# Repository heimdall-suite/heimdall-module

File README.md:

# heimdall-module

ESP32-C3 based module for the transmitter's JR module bay, part of the Heimdall Suite.

## Status

Hardware rev 2 (KiCad 10, `hardware/kicad/`): schematic reviewed and corrected,
board re-placed and re-routed from the first EasyEDA layout. Not built or tested
yet. The EasyEDA originals are kept in `hardware/easyeda-archive/`. No firmware yet.

KiCad 3D renders of rev 2:

| Top, angled | Bottom, angled |
|---|---|
|  |  |

| Top | Bottom (mirrored, as seen from below) |
|---|---|
|  |  |

## Case

The board is shaped for the 3D-printed case `MULTI-Module_Bangood_4-in-1_Case.stl`
(the STL is not in this repo). The figures below were measured from that STL:

- The outline is the case cavity (57 x 41.5 mm) minus 0.3 mm all round. It has
  notches for the two latch housings, which reach 4 mm in from the long walls.
  The top notch merges with the cut-out under the ESP32 module's antenna.
- The four corners are chamfered 45° (2.8 mm legs). The lid screw holes
  (1.7 mm) sit in 3.5 mm bosses in the cavity corners, from about 11 mm above
  the floor upwards. The board has to pass them on the way down to the
  standoffs, and the chamfers leave about 0.47 mm to each boss.
- MH1-MH3 are 2.2 mm holes for 2 mm self-tapping screws into the case's three
  standoffs (4.5 mm, 1.8 mm pilot holes, tops 5 mm above the floor).
  The lid uses the same screws. The copper keeps 3 mm clear of each hole.
- The bay pins come up through the floor opening and the H1 slot into the
  female header on top.
- **H1 position:** taken from three existing JR-bay designs. All three put the
  bay pins about 1.25 mm closer to the end wall than the centre of the case's
  floor opening:
  - DIY Multiprotocol STM32 v1.0t (Eagle)
  - Multiprotocol V2 (Gerbers)
  - ExpressLRS TX_SX1280 (Gerbers)

  This is not yet checked against a real radio.
- The case still needs an opening for the USB-C connector.

`case_place.py` moved the rev 2 parts into the case outline. `spread_place.py`
then spread them for hand soldering: at least 1 mm between courtyards left of the
module, and U1 moved down to the bottom edge. A few pairs on the USB side are
still closer. `route_pcb.py prep` draws the hand routes; Freerouting and the
later `route_pcb.py` steps do the rest.

## Pin assignment (rev 2)

| Function | ESP32-C3 GPIO | Via |
|---|---|---|
| Bay SIGNAL / PPM (H1 pin 1), input | IO4 | D3, R11 4.7k pull-up |
| Bay DATA / S.Port (H1 pin 5), receive | IO5 | D4, R13 4.7k pull-up |
| Bay DATA / S.Port (H1 pin 5), transmit | IO7 | U5 74LVC1G34 + R14 1k |
| Bay HB (H1 pin 2), output | IO8 | D5 (pull low only), R9 doubles as its pull-up |
| I2C SDA / SCL (J1, 10k pull-ups) | GPIO20 / GPIO21 (U0RXD / U0TXD) | |
| Breakout (J1) | IO1, IO3, IO10 | |
| USB D- / D+ | IO18 / IO19 | R4 / R3 33R |
| Strapping | IO2, IO8 (HB), IO9 pulled up 10k; JP1 BOOT bridges IO9 to GND | |

IO0 and IO6 are unused. UART0's pins carry I2C, so the console has to run over
USB-Serial/JTAG.

## Bay interface

The bay lines never connect straight to the ESP32.

- SIGNAL (PPM in) and DATA receive go through a BAT54WS Schottky with its
  cathode at the bay, the same scheme as the DIY Multiprotocol module (STM32
  board v1.0t, BAT48 diodes). The radio can only pull the line low; the high
  level comes from our 3V3 pull-ups (R11, R13), so a radio that drives 5 V
  never reaches the ESP32.
- HB (out) goes through a Schottky with its anode at the bay: the ESP32 can
  only pull it low, R12 (4.7k) pulls it high on the bay side.
- DATA transmit goes through U5, a 74LVC1G34 buffer (5.5 V tolerant, always on),
  and R14 (1k). The UART's idle level holds the line, so the same hardware
  works for CRSF (idle high) and inverted S.Port (idle low); which one is a
  firmware setting. When the radio transmits it overrides the 1k (about
  3.3 mA). Against a 10k pull-up on the radio side, an S.Port idle low sits at
  about 0.3 V (calculated, not measured).

DATA is half duplex on one wire, with separate receive and transmit pins
(IO5/IO7). The receive pin also sees the module's own transmitted bytes, so
firmware has to discard that echo. Inversion is done in the ESP32-C3's UART.
Use IO8 (HB) as an output only after boot: it is a strapping pin, which is
safe here because download mode needs USB, and USB and the bay can't be
connected at the same time.

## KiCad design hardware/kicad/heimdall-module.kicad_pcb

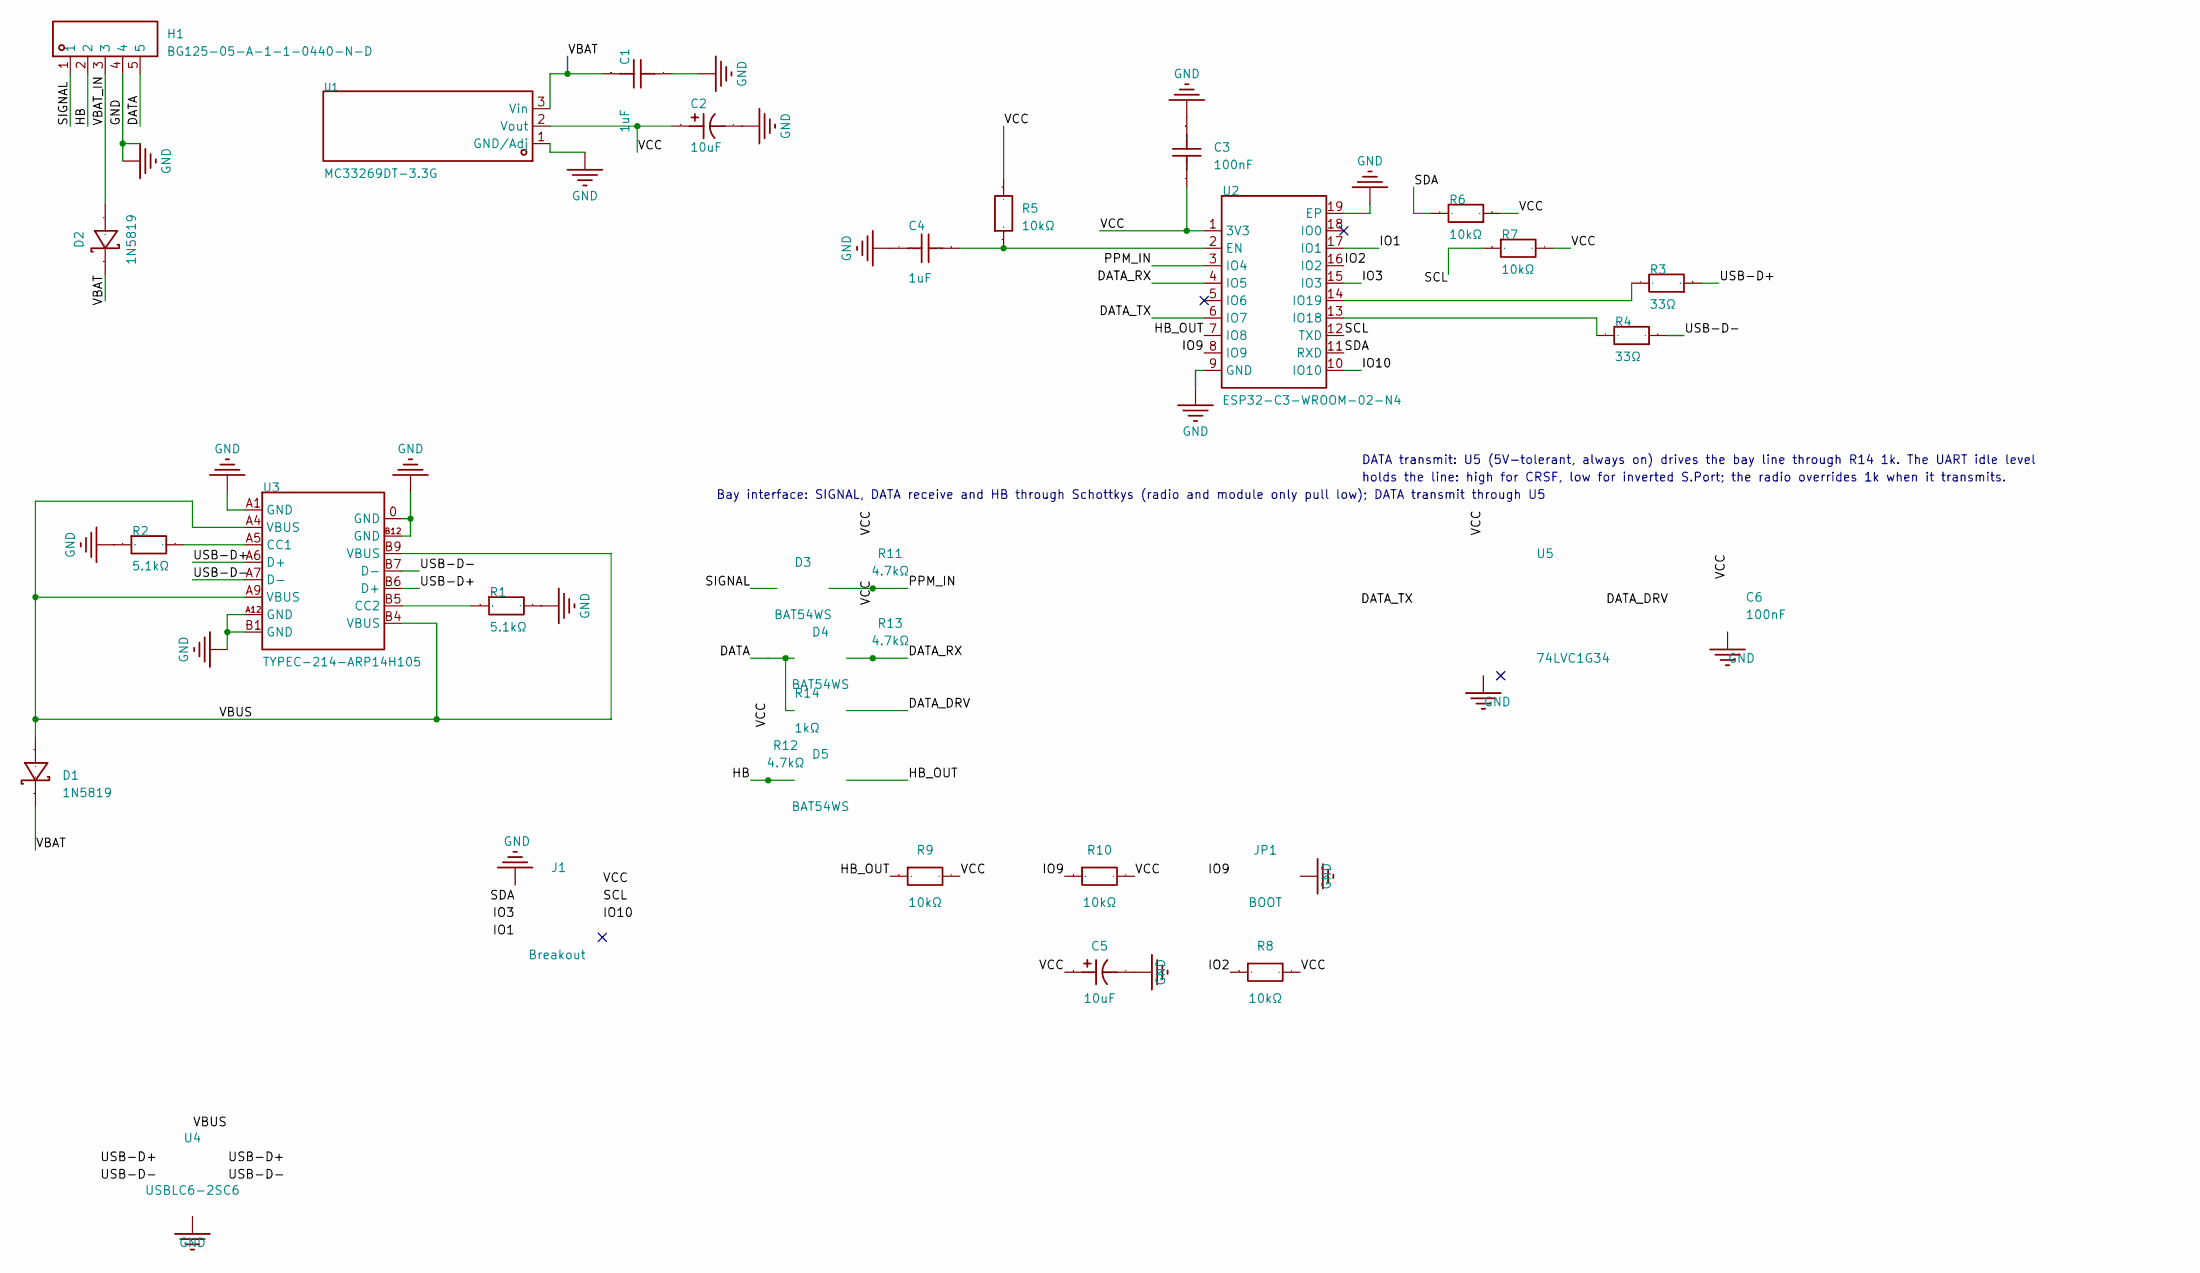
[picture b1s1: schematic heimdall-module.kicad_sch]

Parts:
C1, C4: 1uF; C0805; Manufacturer Part GCM21BR71H105KA03L
C2: 10uF; CASE-A_3216; Manufacturer Part T491A106K010AT; LCSC Part Name 10uF ±10% 10V
C3: 100nF; C0805; Manufacturer Part GRM21B7U1A104JA01L; LCSC Part Name 100nF ±5% 10V
C5: 10uF; CASE-A_3216; Manufacturer Part T491A106K010AT
C6: 100nF; C0805; Manufacturer Part GRM21B7U1A104JA01L
D1: 1N5819; SMA_L4.4-W2.6-LS5.0-RD; Manufacturer Part 1N5819; LCSC Part Name KEXIN(科信)原型号 SS14,后续变更为 1N5819，丝印不变。 电压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
D2: 1N5819; SMA_L4.4-W2.6-LS5.0-RD; Manufacturer Part 1N5819
D3, D4, D5: BAT54WS; D_SOD-323; Manufacturer Part BAT54WS-7-F
H1: BG125-05-A-1-1-0440-N-D; HDR-SMD_5P-P2.54-V-F-LS4.4; Manufacturer Part BG125-05-A-1-1-0440-N-D; LCSC Part Name 1x5P 间距:2.54mm 立贴
J1: Breakout; PinHeader_2x04_P2.54mm_Vertical
JP1: BOOT; SolderJumper-2_P1.3mm_Open_RoundedPad1.0x1.5mm
R1, R2: 5.1kΩ; R0805; Manufacturer Part ERA6AEB512V; LCSC Part Name 薄膜电阻 5.1kΩ ±0.1% 125mW
R3, R4: 33Ω; R0805; Manufacturer Part ERJ6ENF33R0V; LCSC Part Name 33Ω ±1% 125mW 厚膜电阻
R5, R6, R7: 10kΩ; R0805; Manufacturer Part ERJP06F1002V; LCSC Part Name 10kΩ ±1% 500mW 厚膜电阻
R8, R9, R10: 10kΩ; R0805; Manufacturer Part ERJP06F1002V
R11, R12, R13: 4.7kΩ; R0805; Manufacturer Part ERJ-6ENF4701V
R14: 1kΩ; R0805; Manufacturer Part ERJ-6ENF1001V
U1: MC33269DT-3.3G; TO-252-2_L6.6-W6.1-P4.57-LS9.9-BR-CW; Manufacturer Part MC33269DT-3.3G; LCSC Part Name 3.3V 800mA 20V
U2: ESP32-C3-WROOM-02-N4; BULETM-SMD_ESPRESSIF_ESP32-C3-WROOM-02-N4-4MB; Manufacturer Part ESP32-C3-WROOM-02-N4; LCSC Part Name 不带固件 2.4GHz Wi-Fi（802.11b/g/n）+ 蓝牙5模组
U3: TYPEC-214-ARP14H105; USB-TYPE-C-TH_TYPEC-214-ARP14H105; Manufacturer Part TYPEC-214-ARP14H105; LCSC Part Name Type-C 母 直插
U4: USBLC6-2SC6; SOT-23-6; Manufacturer Part USBLC6-2SC6
U5: 74LVC1G34; SOT-23-5; Manufacturer Part SN74LVC1G34DBVR

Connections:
/DATA: D4.1 (K), H1.5, R14.1
/DATA_DRV: R14.2, U5.4
/DATA_RX: D4.2 (A), R13.2, U2.4 (IO5)
/DATA_TX: U2.6 (IO7), U5.2
/HB: D5.2 (A), H1.2, R12.2
/HB_OUT: D5.1 (K), R9.1, U2.7 (IO8)
/IO1: J1.7, U2.17 (IO1)
/IO2: R8.1, U2.16 (IO2)
/IO3: J1.5, U2.15 (IO3)
/IO9: JP1.1 (A), R10.1, U2.8 (IO9)
/IO10: J1.6, U2.10 (IO10)
/PPM_IN: D3.2 (A), R11.2, U2.3 (IO4)
/SCL: J1.4, R7.1, U2.12 (TXD)
/SDA: J1.3, R6.2, U2.11 (RXD)
/SIGNAL: D3.1 (K), H1.1
/USB-D+: R3.1, U3.A6 (D+), U3.B6 (D+), U4.1 (I/O1), U4.6 (I/O1)
/USB-D-: R4.1, U3.A7 (D-), U3.B7 (D-), U4.3 (I/O2), U4.4 (I/O2)
/VBAT: C1.1, D1.1 (C), D2.1 (C), U1.3 (Vin)
/VBAT_IN: D2.2 (A), H1.3
/VBUS: D1.2 (A), U3.A4 (VBUS), U3.A9 (VBUS), U3.B4 (VBUS), U3.B9 (VBUS), U4.5 (VBUS)
/VCC: C2.1, C3.2, C5.1, C6.1, J1.2, R5.2, R6.1, R7.2, R8.2, R9.2, R10.2, R11.1, R12.1, R13.1, U1.2 (Vout), U2.1 (3V3), U5.5 (VCC)
GND: C1.2, C2.2, C3.1, C4.2, C5.2, C6.2, H1.4, J1.1, JP1.2 (B), R1.2, R2.1, U1.1 (GND/Adj), U2.9 (GND), U2.19 (EP), U3.0 (GND), U3.A1 (GND), U3.A12 (GND), U3.B1 (GND), U3.B12 (GND), U4.2 (GND), U5.3 (GND)
unnamed: C4.1, R5.1, U2.2 (EN)
unnamed: R4.2, U2.13 (IO18)
unnamed: R3.2, U2.14 (IO19)
unnamed: R2.2, U3.A5 (CC1)
unnamed: R1.1, U3.B5 (CC2)

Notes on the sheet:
Bay interface: SIGNAL, DATA receive and HB through Schottkys (radio and module only pull low); DATA transmit through U5
DATA transmit: U5 (5V-tolerant, always on) drives the bay line through R14 1k. The UART idle level
holds the line: high for CRSF, low for inverted S.Port; the radio overrides 1k when it transmits.

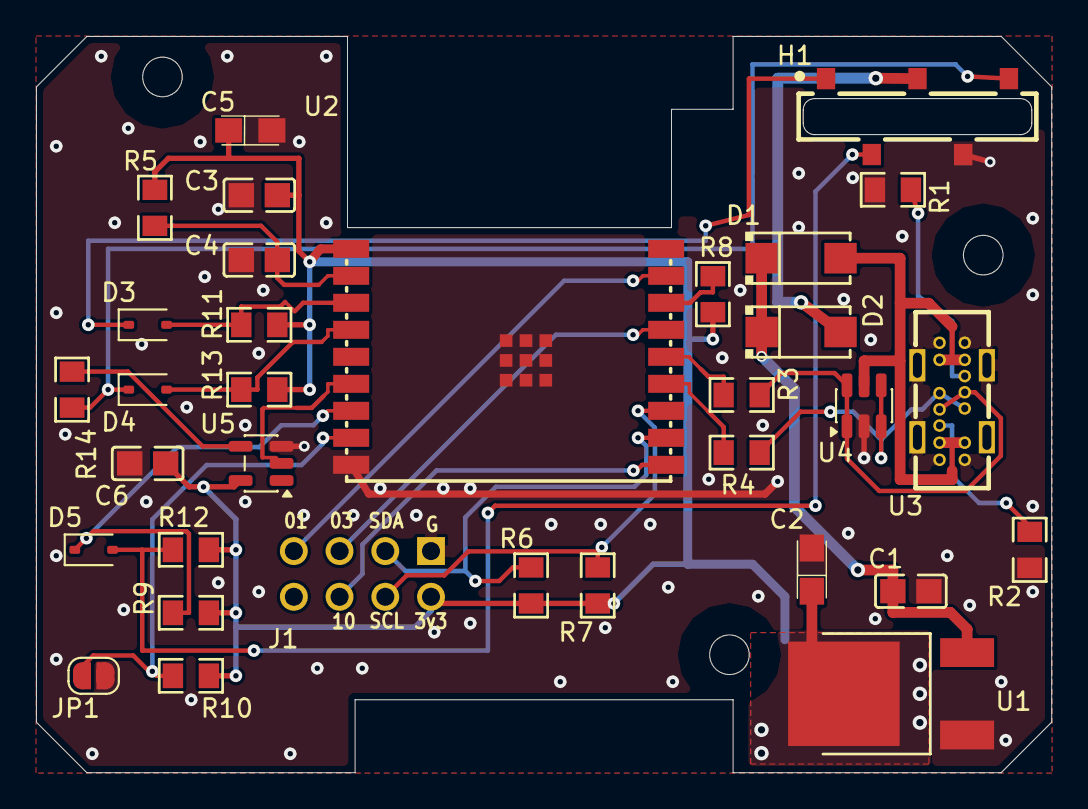
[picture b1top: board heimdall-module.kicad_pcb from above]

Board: 2 copper layers, 56.4 x 40.9 mm, 36 parts (0 on the bottom side), 27 nets.

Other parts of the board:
MH1, MH2, MH3: M2; MountingHole_2.2mm_M2_ISO14580

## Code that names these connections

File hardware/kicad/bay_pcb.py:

"""Bay interface on the PCB: sync to the netlist (D5 out; U5/C6 in, R17 moved), place, strip copper.
Run with KiCad's python from hardware/kicad:  python bay_pcb.py NETLIST.xml"""
import sys, pcbnew, xml.etree.ElementTree as ET

B = 'heimdall-module.kicad_pcb'
STD = r'C:/Users/svefre/AppData/Local/Programs/KiCad/10.0/share/kicad/footprints'
PRJLIB = 'heimdall-m-easyedapro'
IO = pcbnew.PCB_IO_KICAD_SEXPR()
MM = pcbnew.FromMM
V = lambda x, y: pcbnew.VECTOR2I(MM(x), MM(y))

b = pcbnew.LoadBoard(B)
net = ET.parse(sys.argv[1]).getroot()
comps = {c.get('ref'): c for c in net.iter('comp')}
pinnet = {(n2.get('ref'), n2.get('pin')): n.get('name') for n in net.iter('net') for n2 in n.iter('node')}

def load(fpid):
    nick, name = fpid.split(':')
    f = IO.FootprintLoad(PRJLIB + '.pretty' if nick == PRJLIB else '%s/%s.pretty' % (STD, nick), name)
    f.SetFPID(pcbnew.LIB_ID(nick, name))
    return f

# rows follow module pins 3..6 (IO4 PPM_IN, IO5 DATA_RX, IO6 DATA_TX, IO7 HB_OUT)
RA, RB, RC, RD = 101.9, 103.95, 106.0, 108.05
XD, XB, XM = 127.7, 123.1, 132.4
PLACE = {
    'D3': (XD, RA, 0), 'D4': (XD, RB, 0),            # K at the bay (left)
    'R14': (XM, RA, 180), 'R16': (XM, RB, 180),      # MCU-side pull-ups, VCC pad right
    # DATA transmit in the band below row B: U5 beside module pads 6/7, C6 next to it, R17 by the DATA via
    'U5': (133.4, 106.7, 180), 'C6': (129.25, 106.9, 180), 'R17': (125.2, 107.3, 0),
    # HB a step lower to make room: D6 (A at the bay, left) and its pull-up R15
    'D6': (XD, 109.3, 180), 'R15': (122.7, 109.3, 0),
    'R12': (131.4, 109.9, 0), 'R13': (131.4, 112.1, 0),   # 0.3 lower, so HB_OUT and U5's VCC via fit above
}

dead = list(b.GetTracks()) + list(b.Zones())
for f in b.GetFootprints():
    ref = f.GetReference()
    if ref and ref not in comps and not f.IsBoardOnly():
        dead.append(f); print('remove', ref)

for ref, c in comps.items():
    f = b.FindFootprintByReference(ref)
    if not f:
        f = load(c.findtext('footprint')); f.SetReference(ref); b.Add(f)
        f.SetPath(pcbnew.KIID_PATH('/' + c.find('tstamps').text))
        f.SetSheetname('/'); f.SetSheetfile('heimdall-module.kicad_sch')
        print('add', ref)
    if ref in PLACE:      # new or changed parts: value and fields from the schematic
        f.SetValue(c.findtext('value'))
        for fld in c.iter('field'):
            if fld.get('name') not in ('Footprint', 'Datasheet', 'Description'):
                f.SetField(fld.get('name'), fld.text or '')
                f.GetField(fld.get('name')).SetVisible(False)
    if ref in PLACE:
        x, y, r = PLACE[ref]
        f.SetPosition(V(x, y)); f.SetOrientationDegrees(r)
        f.Reference().SetLayer(pcbnew.F_Fab)   # too dense for silk refs
    for p in f.Pads():
        name = pinnet.get((ref, p.GetNumber()))
        if name is None:
            p.SetNetCode(0); continue
        ni = b.FindNet(name)
        if ni is None:
            ni = pcbnew.NETINFO_ITEM(b, name); b.Add(ni)
        p.SetNet(ni)

# JP1's reference would sit on D6 (one row lower now): left of the jumper instead
b.FindFootprintByReference('JP1').Reference().SetPosition(V(122.8, 112.0))

for it in dead:
    b.Remove(it)
pcbnew.SaveBoard(B, b)
for r in sorted(PLACE):
    f = b.FindFootprintByReference(r)
    print(r, [(p.GetNumber(), p.GetNetname(), round(pcbnew.ToMM(p.GetPosition().x), 2), round(pcbnew.ToMM(p.GetPosition().y), 2)) for p in f.Pads()])
